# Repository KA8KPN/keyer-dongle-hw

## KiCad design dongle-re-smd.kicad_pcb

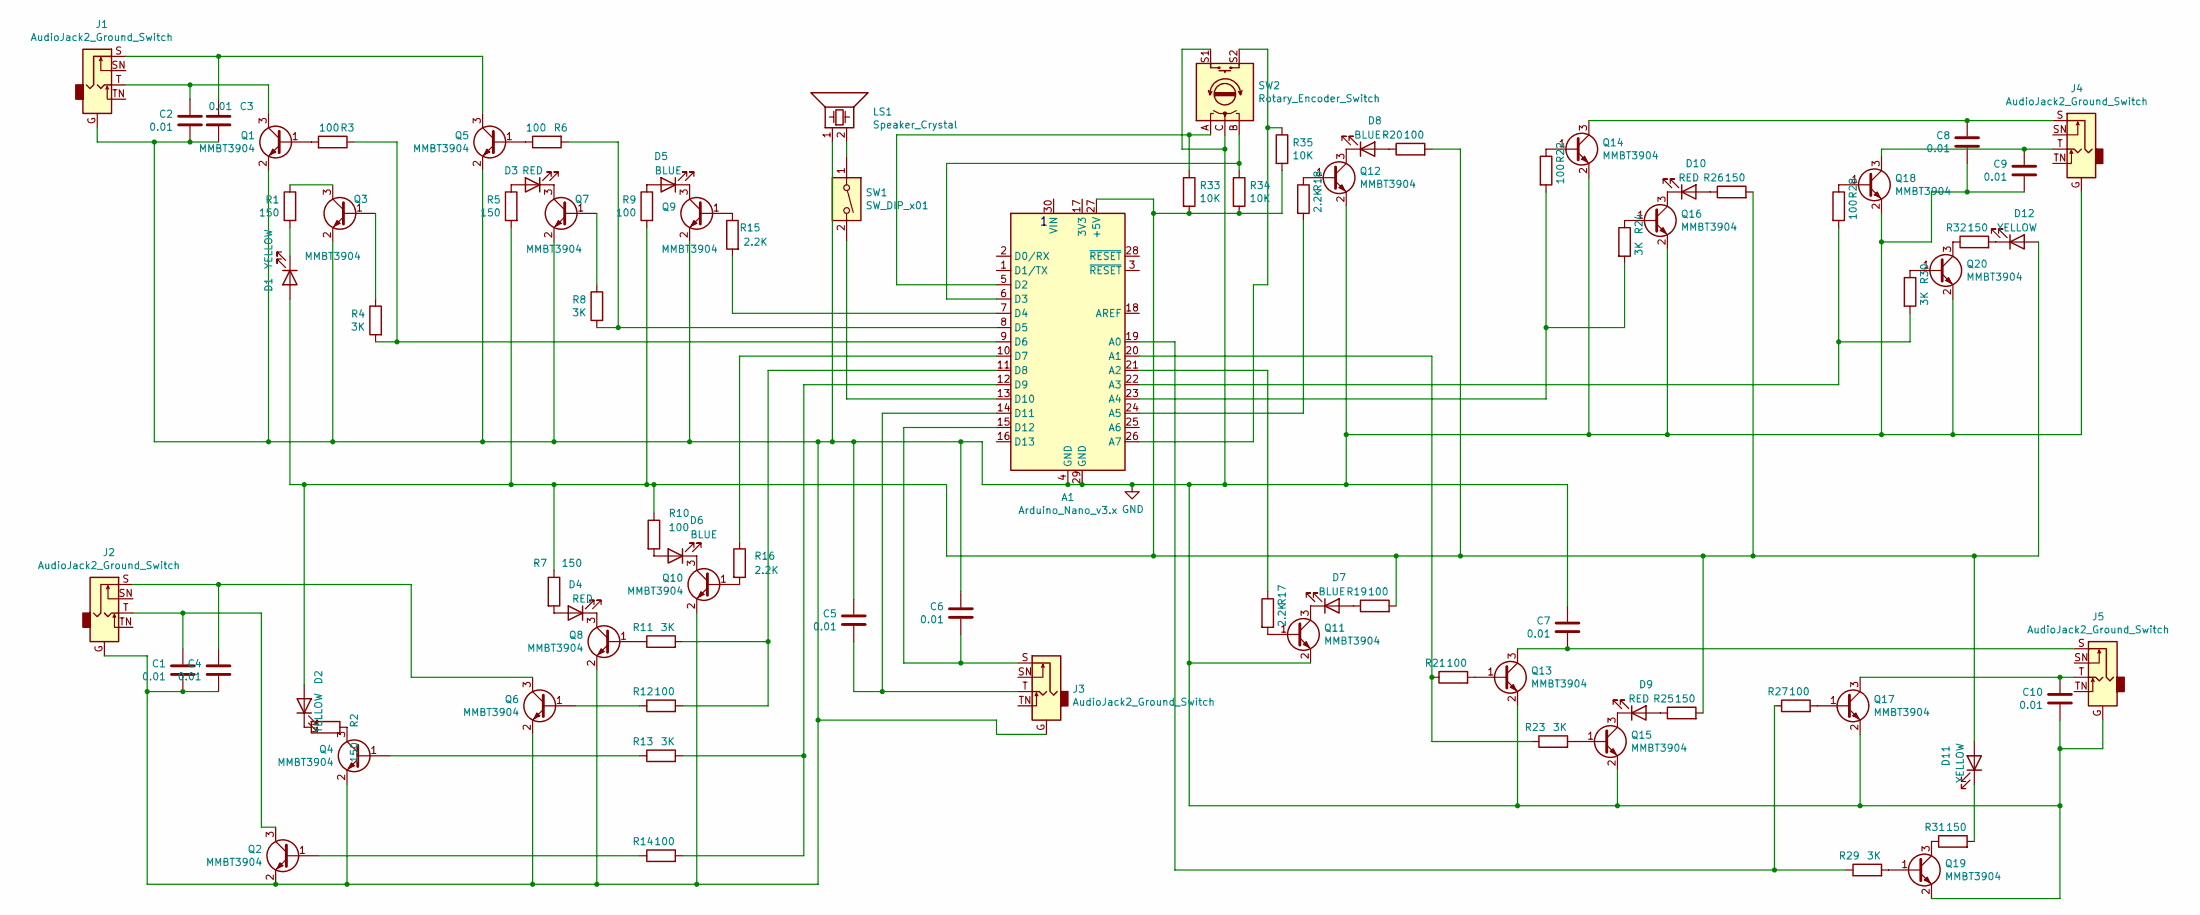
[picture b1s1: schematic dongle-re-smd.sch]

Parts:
A1: Arduino_Nano_v3.x; Arduino_Nano
C1, C2, C3, C4, C5, C6, C7, C8, C9, C10: 0.01; C_0805_2012Metric
D1, D2, D11, D12: YELLOW; LED_0805_2012Metric
D3, D4, D9, D10: RED; LED_0805_2012Metric
D5, D6, D7, D8: BLUE; LED_0805_2012Metric
J1, J2, J3, J4, J5: AudioJack2_Ground_Switch; Jack_3.5mm_PJ307_Horizontal
LS1: Speaker_Crystal; Buzzer_15x7.5RM7.6
Q1, Q2, Q3, Q4, Q5, Q6, Q7, Q8, Q9, Q10, Q11, Q12, Q13, Q14, Q15, Q16, Q17, Q18, Q19, Q20: MMBT3904; SOT-23
R1, R2, R5, R7, R25, R26, R31, R32: 150; R_0805_2012Metric
R3, R6, R9, R10, R12, R14, R19, R20, R21, R22, R27, R28: 100; R_0805_2012Metric
R4, R8, R11, R13, R23, R24, R29, R30: 3K; R_0805_2012Metric
R15, R16, R17, R18: 2.2K; R_0805_2012Metric
R33, R34, R35: 10K; R_0805_2012Metric
SW1: SW_DIP_x01; SW_DIP_SPSTx01_Slide_6.7x4.1mm_W7.62mm_P2.54mm_LowProfile
SW2: Rotary_Encoder_Switch; RotaryEncoder_Alps_EC11E-Switch_Vertical_H20mm

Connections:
GND: A1.4 (GND), A1.29 (GND), C1.2, C2.2, C3.2, C4.2, C5.1, C6.1, C7.1, C8.2, C9.2, C10.2, J1.G, J2.G, J3.G, J4.G, J5.G, LS1.1, Q1.2 (E), Q2.2 (E), Q3.2 (E), Q4.2 (E), Q5.2 (E), Q6.2 (E), Q7.2 (E), Q8.2 (E), Q9.2 (E), Q10.2 (E), Q11.2 (E), Q12.2 (E), Q13.2 (E), Q14.2 (E), Q15.2 (E), Q16.2 (E), Q17.2 (E), Q18.2 (E), Q19.2 (E), Q20.2 (E), SW2.C, SW2.S1
unnamed: A1.5 (D2), R33.1, SW2.A
unnamed: A1.6 (D3), R34.1, SW2.B
unnamed: A1.7 (D4), R15.2
unnamed: A1.8 (D5), R6.2, R8.2
unnamed: A1.9 (D6), R3.1, R4.2
unnamed: A1.10 (D7), R16.1
unnamed: A1.11 (D8), R11.2, R12.2
unnamed: A1.12 (D9), R13.2, R14.2
unnamed: A1.13 (D10), SW1.2
unnamed: A1.14 (D11), C5.2, J3.T
unnamed: A1.15 (D12), C6.2, J3.S
unnamed: A1.19 (A0), R27.1, R29.1
unnamed: A1.20 (A1), R21.1, R23.1
unnamed: A1.21 (A2), R17.1
unnamed: A1.22 (A3), R28.2, R30.2
unnamed: A1.23 (A4), R22.2, R24.2
unnamed: A1.24 (A5), R18.2
unnamed: A1.26 (A7), R35.1, SW2.S2
unnamed: A1.27 (+5V), D1.2 (A), D2.2 (A), D11.2 (A), D12.2 (A), R5.2, R7.1, R9.2, R10.1, R19.2, R20.2, R25.2, R26.2, R33.2, R34.2, R35.2
unnamed: C1.1, J2.T, Q2.3 (C)
unnamed: C2.1, J1.T, Q1.3 (C)
unnamed: C3.1, J1.S, Q5.3 (C)
unnamed: C4.1, J2.S, Q6.3 (C)
unnamed: C7.2, J5.S, Q13.3 (C)
unnamed: C8.1, J4.S, Q14.3 (C)
unnamed: C9.1, J4.T, Q18.3 (C)
unnamed: C10.1, J5.T, Q17.3 (C)
unnamed: D1.1 (K), R1.2
unnamed: D2.1 (K), R2.2
unnamed: D3.1 (K), Q7.3 (C)
unnamed: D3.2 (A), R5.1
unnamed: D4.1 (K), Q8.3 (C)
unnamed: D4.2 (A), R7.2
unnamed: D5.1 (K), Q9.3 (C)
unnamed: D5.2 (A), R9.1
unnamed: D6.1 (K), Q10.3 (C)
unnamed: D6.2 (A), R10.2
unnamed: D7.1 (K), Q11.3 (C)
unnamed: D7.2 (A), R19.1
unnamed: D8.1 (K), Q12.3 (C)
unnamed: D8.2 (A), R20.1
unnamed: D9.1 (K), Q15.3 (C)
unnamed: D9.2 (A), R25.1
unnamed: D10.1 (K), Q16.3 (C)
unnamed: D10.2 (A), R26.1
unnamed: D11.1 (K), R31.2
unnamed: D12.1 (K), R32.2
unnamed: LS1.2, SW1.1
unnamed: Q1.1 (B), R3.2
unnamed: Q2.1 (B), R14.1
unnamed: Q3.1 (B), R4.1
unnamed: Q3.3 (C), R1.1
unnamed: Q4.1 (B), R13.1
unnamed: Q4.3 (C), R2.1
unnamed: Q5.1 (B), R6.1
unnamed: Q6.1 (B), R12.1
unnamed: Q7.1 (B), R8.1
unnamed: Q8.1 (B), R11.1
unnamed: Q9.1 (B), R15.1
unnamed: Q10.1 (B), R16.2
unnamed: Q11.1 (B), R17.2
unnamed: Q12.1 (B), R18.1
unnamed: Q13.1 (B), R21.2
unnamed: Q14.1 (B), R22.1
unnamed: Q15.1 (B), R23.2
unnamed: Q16.1 (B), R24.1
unnamed: Q17.1 (B), R27.2
unnamed: Q18.1 (B), R28.1
unnamed: Q19.1 (B), R29.2
unnamed: Q19.3 (C), R31.1
unnamed: Q20.1 (B), R30.1
unnamed: Q20.3 (C), R32.1

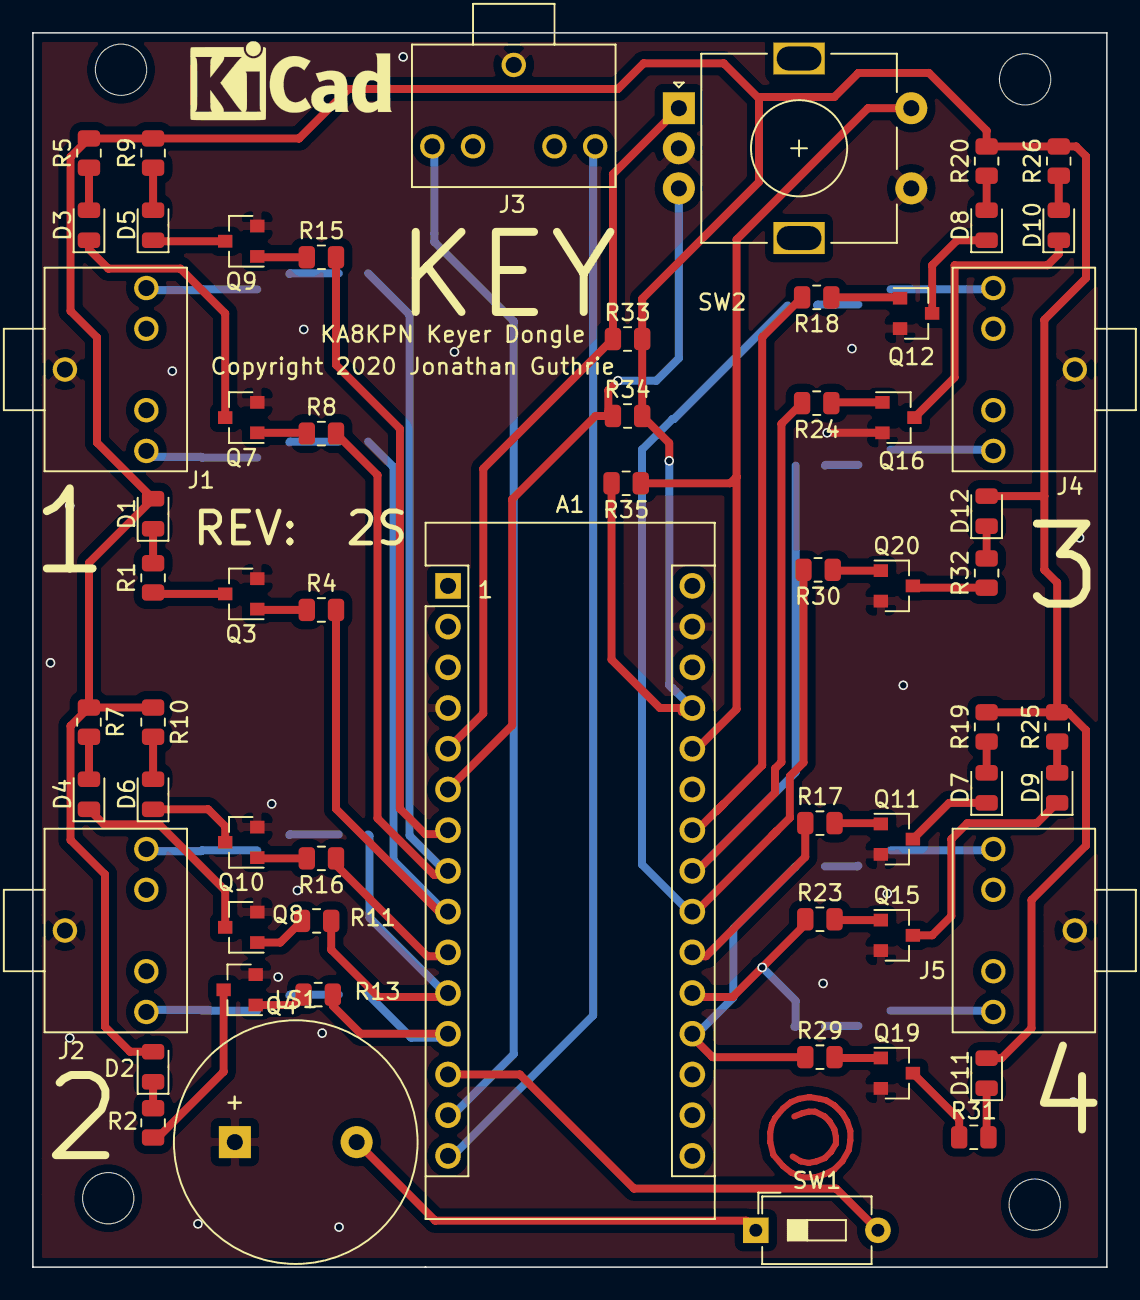
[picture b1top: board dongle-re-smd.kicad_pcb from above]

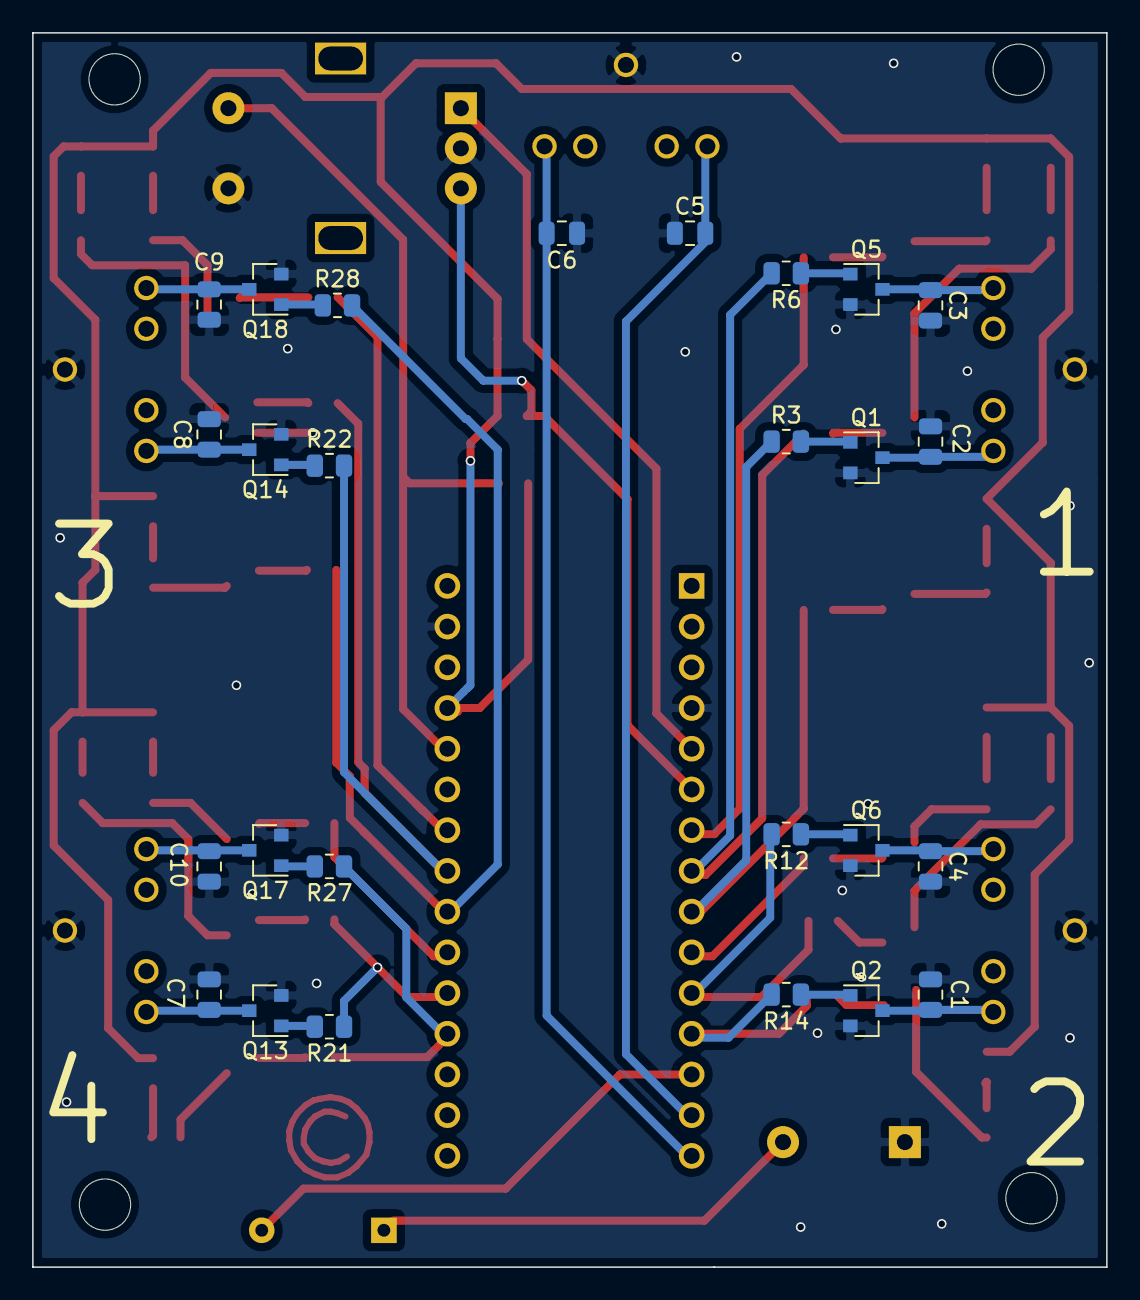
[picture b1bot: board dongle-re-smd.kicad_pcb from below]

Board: 2 copper layers, 67.0 x 77.0 mm, 86 parts (26 on the bottom side), 73 nets.

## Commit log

2020-12-05 Add the hardware design to the repository
2020-12-05 Change the footprints on the LED's to indicate which pad is for the cathode so that they can be soldered more easily.
2021-02-03 Fix an error in the schematic and update the PC board layout.
    The emitter of Q16 needs to be grounded or port 3's red LED doesn't work.
2021-02-04 While I'm at it, I can also fix the footprint of the buzzer, which doesn't match the parts I actually have, and fix another issue when I ran a DRC
2021-03-20 Fix a small error (the word "key" is overlaid the digit 4 on the silkscreen on the front of the board) and update the project xml file.
2021-03-21 Add a bill of materials for the rotary-encoder based board build with surface-mount devices

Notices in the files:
dongle-re-smd.kicad_pcb:
Copyright 2020 Jonathan Guthrie
